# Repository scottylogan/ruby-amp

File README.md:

My version of the [Ruby Amp](http://www.runoffgroove.com/ruby.html).

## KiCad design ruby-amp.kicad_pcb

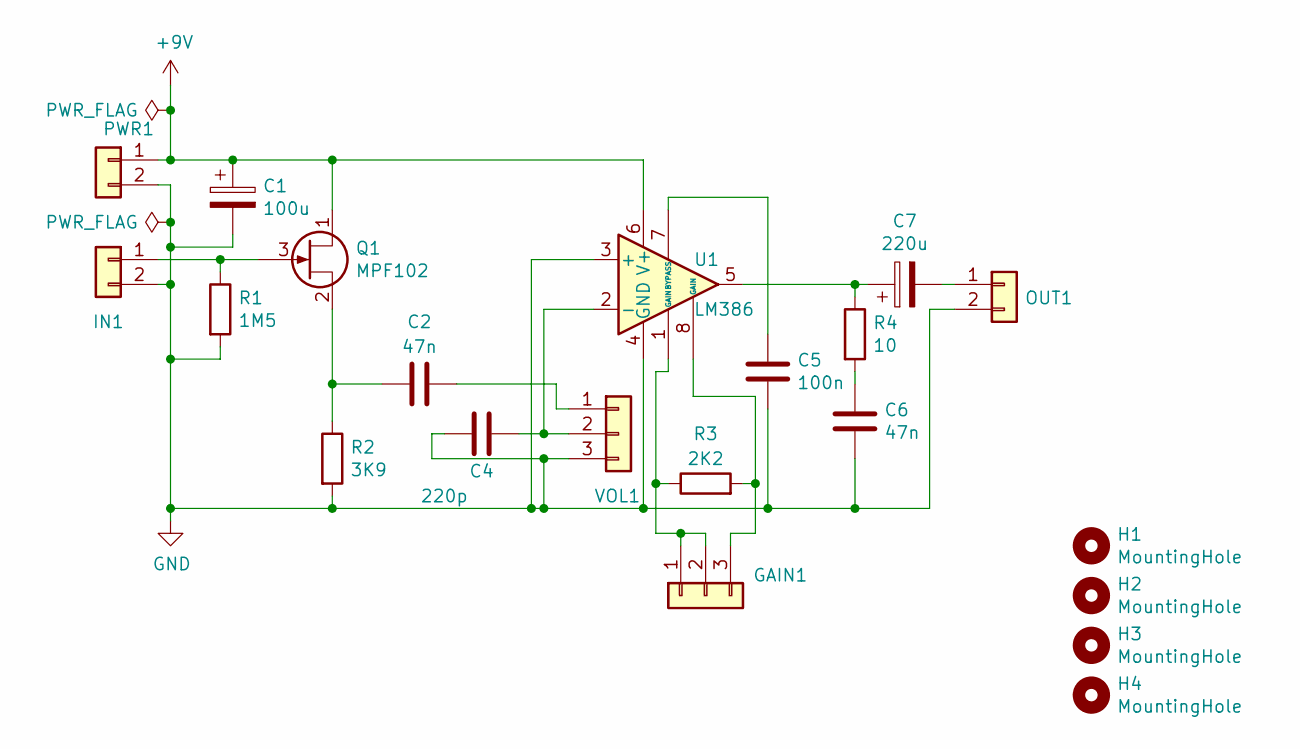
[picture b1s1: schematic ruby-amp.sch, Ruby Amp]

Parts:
C1: 100u; CP_Radial_D5.0mm_P2.50mm
C2, C6: 47n; C_Disc_D3.0mm_W2.0mm_P2.50mm
C4: 220p; C_Disc_D3.0mm_W2.0mm_P2.50mm
C5: 100n; C_Disc_D3.0mm_W2.0mm_P2.50mm
C7: 220u; CP_Radial_D5.0mm_P2.50mm
GAIN1: Conn_01x03; PinHeader_1x03_P2.54mm_Vertical
H1, H2, H3, H4: MountingHole; MountingHole_2.2mm_M2
IN1: Conn_01x02; PinHeader_1x02_P2.54mm_Vertical
OUT1: Conn_01x02; PinHeader_1x02_P2.54mm_Vertical
PWR1: Conn_01x02; PinHeader_1x02_P2.54mm_Vertical
Q1: MPF102; TO-92
R1: 1M5; R_Axial_DIN0204_L3.6mm_D1.6mm_P5.08mm_Horizontal
R2: 3K9; R_Axial_DIN0204_L3.6mm_D1.6mm_P5.08mm_Horizontal
R3: 2K2; R_Axial_DIN0204_L3.6mm_D1.6mm_P5.08mm_Horizontal
R4: 10; R_Axial_DIN0204_L3.6mm_D1.6mm_P5.08mm_Horizontal
U1: LM386; DIP-8_W7.62mm_Socket
VOL1: Conn_01x03; PinHeader_1x03_P2.54mm_Vertical

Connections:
+9V: C1.1, PWR1.1, Q1.1 (D), U1.6 (V+)
GND: C1.2, C4.2, C5.2, C6.2, IN1.2, OUT1.2, PWR1.2, R1.2, R2.2, U1.3 (+), U1.4 (GND), VOL1.3
unnamed: C2.1, Q1.2 (S), R2.1
unnamed: C2.2, VOL1.1
unnamed: C4.1, U1.2 (-), VOL1.2
unnamed: C5.1, U1.7 (BYPASS)
unnamed: C6.1, R4.2
unnamed: C7.1, R4.1, U1.5
unnamed: C7.2, OUT1.1
unnamed: GAIN1.1, GAIN1.2, R3.1, U1.1 (GAIN)
unnamed: GAIN1.3, R3.2, U1.8 (GAIN)
unnamed: IN1.1, Q1.3 (G), R1.1

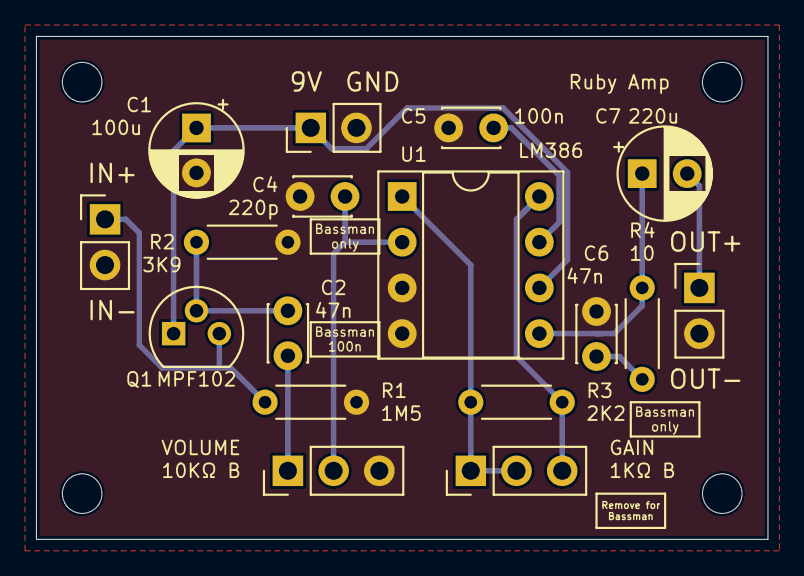
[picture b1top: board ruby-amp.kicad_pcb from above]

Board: 2 copper layers, 40.6 x 27.9 mm, 21 parts (0 on the bottom side), 12 nets.

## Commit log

2025-04-16 added LICENSE
